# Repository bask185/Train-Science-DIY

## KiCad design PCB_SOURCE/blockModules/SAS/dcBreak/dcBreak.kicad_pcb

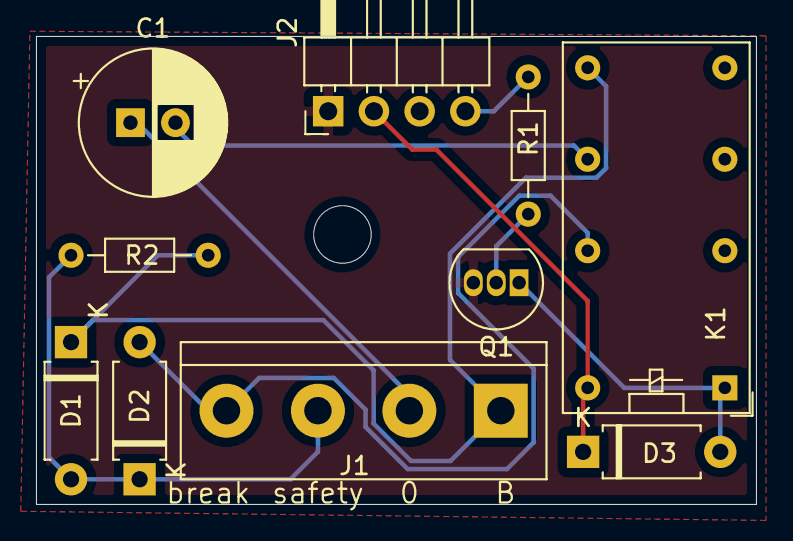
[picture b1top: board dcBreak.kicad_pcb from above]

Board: 2 copper layers, 40.0 x 26.0 mm, 11 parts (0 on the bottom side), 10 nets.

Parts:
C1: CP; CP_Radial_D8.0mm_P2.50mm
D1, D2, D3: D; D_A-405_P7.62mm_Horizontal
J1: Screw_Terminal_01x02; TerminalBlock_bornier-4_P5.08mm
J2: Conn_01x04_Male; PinHeader_1x04_P2.54mm_Horizontal
K1: AZ850-x; Relay_DPDT_Omron_G5V-2
Q1: BC547; TO-92_Inline
R1, R2: R; R_Axial_DIN0204_L3.6mm_D1.6mm_P7.62mm_Horizontal
d: MountingHole_3.2mm_M3

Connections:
+5V: D3.1, J2.2, K1.10
/B: D1.1, J1.1, K1.9, R2.1
/O: C1.1, J1.2
/break: D2.2, J1.4, K1.8
/safety: D1.2, D2.1, J1.3, R2.2
GND: J2.1, Q1.3
unnamed: C1.2, K1.7
unnamed: D3.2, K1.1, Q1.1
unnamed: J2.4, R1.2
unnamed: Q1.2, R1.1

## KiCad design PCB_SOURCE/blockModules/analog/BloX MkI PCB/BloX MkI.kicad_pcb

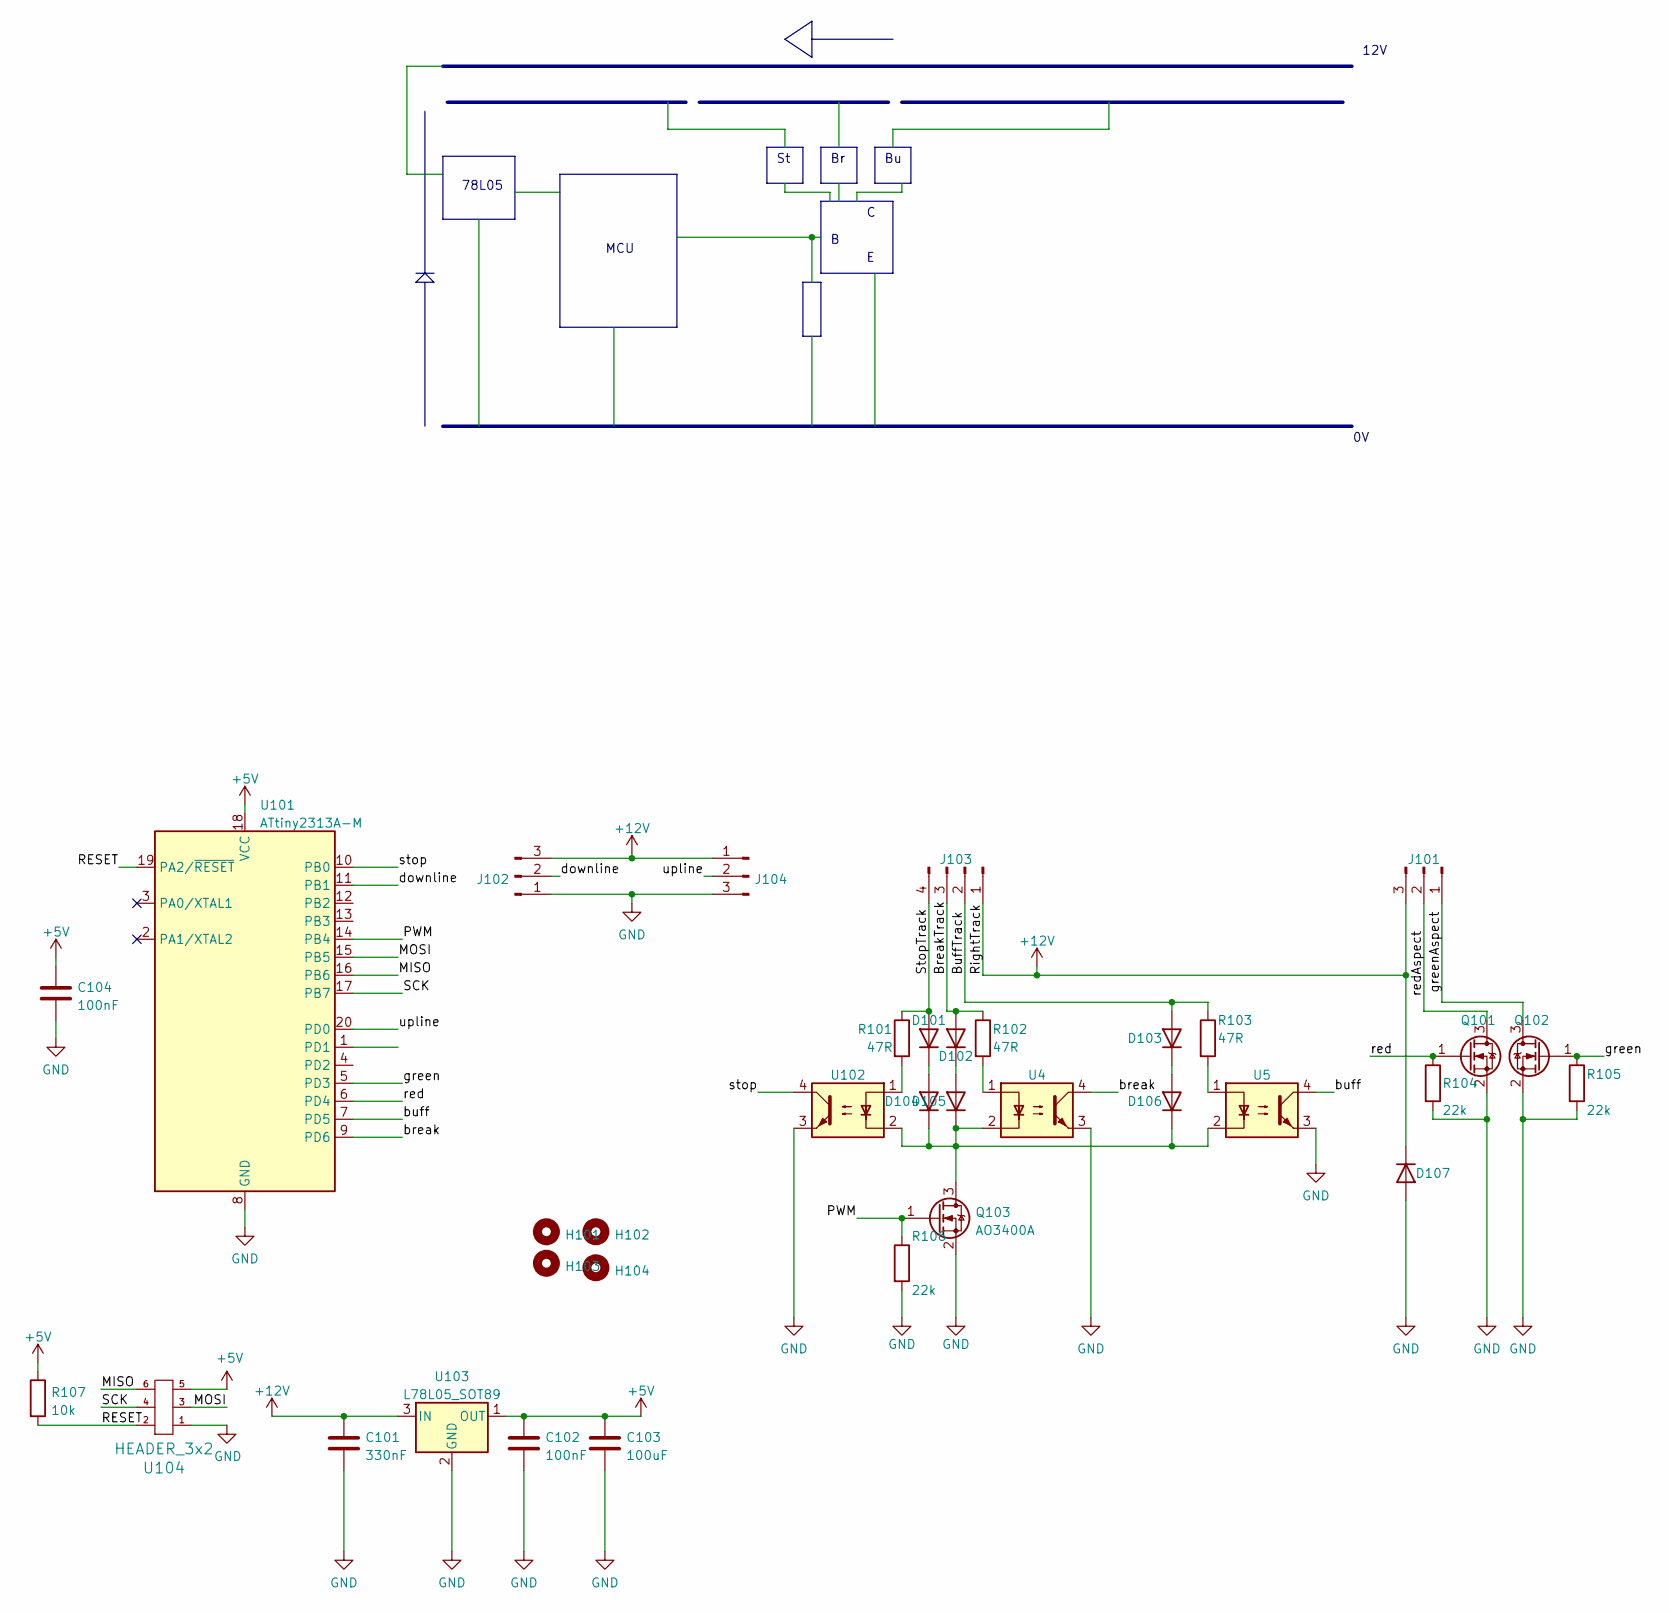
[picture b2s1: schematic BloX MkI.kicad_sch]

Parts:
C101: 330nF; C_0603_1608Metric_Pad1.08x0.95mm_HandSolder; JLCPCB Part# C1615
C102, C104: 100nF; C_0603_1608Metric_Pad1.08x0.95mm_HandSolder; JLCPCB Part# C14663
C103: 100uF; C_1206_3216Metric_Pad1.33x1.80mm_HandSolder; JLCPCB Part# C15008
D101, D102, D103, D104, D105, D106, D107: SM4007; D_SOD-123F; JLCPCB Part# C64898
H101, H102, H103, H104: MountingHole; MountingHole_3.2mm_M3
J101, J102, J104: Conn_01x03_Male; PhoenixContact_MC_1,5_3-G-3.81_1x03_P3.81mm_Horizontal
J103: Conn_01x04_Male; PhoenixContact_MC_1,5_4-G-3.81_1x04_P3.81mm_Horizontal
Q101, Q102, Q103: AO3400A; SOT-23; JLCPCB Part# C20917
R101, R102, R103: 47R; R_0805_2012Metric_Pad1.20x1.40mm_HandSolder; JLCPCB Part# C17714
R104, R105, R106: 22k; R_0805_2012Metric_Pad1.20x1.40mm_HandSolder; JLCPCB Part# C17560
R107: 10k; R_0603_1608Metric_Pad0.98x0.95mm_HandSolder; JLCPCB Part# C25804
U4, U5, U102: SFH617A-3X017T; SMDIP-4_W9.53mm_Clearance8mm
U101: ATtiny2313A-M; MLF-20-1EP_4x4mm_P0.5mm_EP2.6x2.6mm; JLCPCB Part# C185530
U103: L78L05_SOT89; SOT-89-3; JLCPCB Part# C71136
U104: HEADER_3x2; PinSocket_2x03_P1.27mm_Vertical

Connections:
+5V: C102.1, C103.1, C104.1, R107.1, U101.18 (VCC), U103.1 (OUT), U104.5
+12V: C101.1, D107.1 (K), J101.3, J102.3, J103.1, J104.1, U103.3 (IN)
/BreakTrack: D102.2 (A), J103.3, R102.1
/BuffTrack: D103.2 (A), J103.2, R103.1
/MISO: U101.16 (PB6), U104.6
/MOSI: U101.15 (PB5), U104.3
/PWM: Q103.1 (G), R106.1, U101.14 (PB4)
/RESET: R107.2, U101.19 (PA2/~RESET), U104.2
/SCK: U101.17 (PB7), U104.4
/StopTrack: D101.2 (A), J103.4, R101.1
/break: U4.4, U101.9 (PD6)
/buff: U5.4, U101.7 (PD5)
/downline: J102.2, U101.11 (PB1)
/green: Q102.1 (G), R105.1, U101.5 (PD3)
/greenAspect: J101.1, Q102.3 (D)
/red: Q101.1 (G), R104.1, U101.6 (PD4)
/redAspect: J101.2, Q101.3 (D)
/stop: U101.10 (PB0), U102.4
/upline: J104.2, U101.20 (PD0)
GND: C101.2, C102.2, C103.2, C104.2, D107.2 (A), J102.1, J104.3, Q101.2 (S), Q102.2 (S), Q103.2 (S), R104.2, R105.2, R106.2, U4.3, U5.3, U101.8 (GND), U101.21 (GND), U102.3, U103.2 (GND), U104.1
unnamed: D101.1 (K), D104.2 (A)
unnamed: D102.1 (K), D105.2 (A)
unnamed: D103.1 (K), D106.2 (A)
unnamed: D104.1 (K), D105.1 (K), D106.1 (K), Q103.3 (D), U4.2, U5.2, U102.2
unnamed: R101.2, U102.1
unnamed: R102.2, U4.1
unnamed: R103.2, U5.1

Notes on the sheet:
78L05
MCU
12V

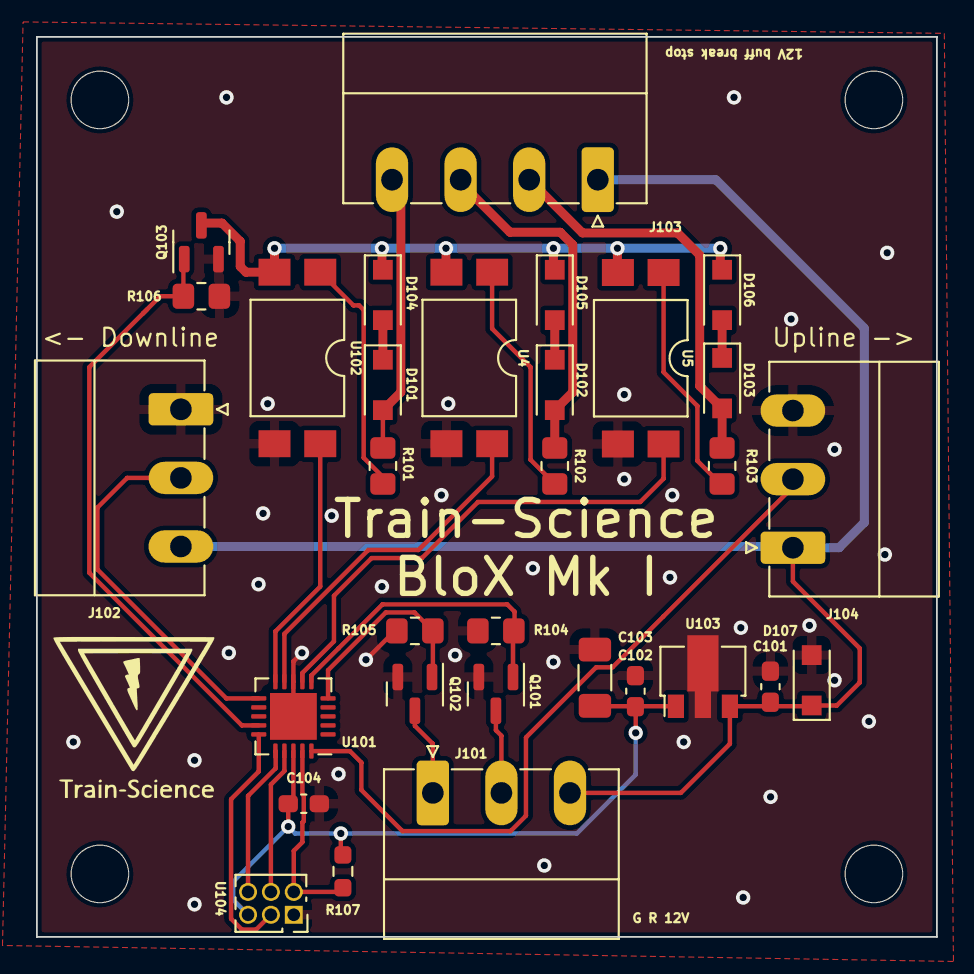
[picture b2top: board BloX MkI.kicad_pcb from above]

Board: 2 copper layers, 50.0 x 50.0 mm, 35 parts (0 on the bottom side), 27 nets.

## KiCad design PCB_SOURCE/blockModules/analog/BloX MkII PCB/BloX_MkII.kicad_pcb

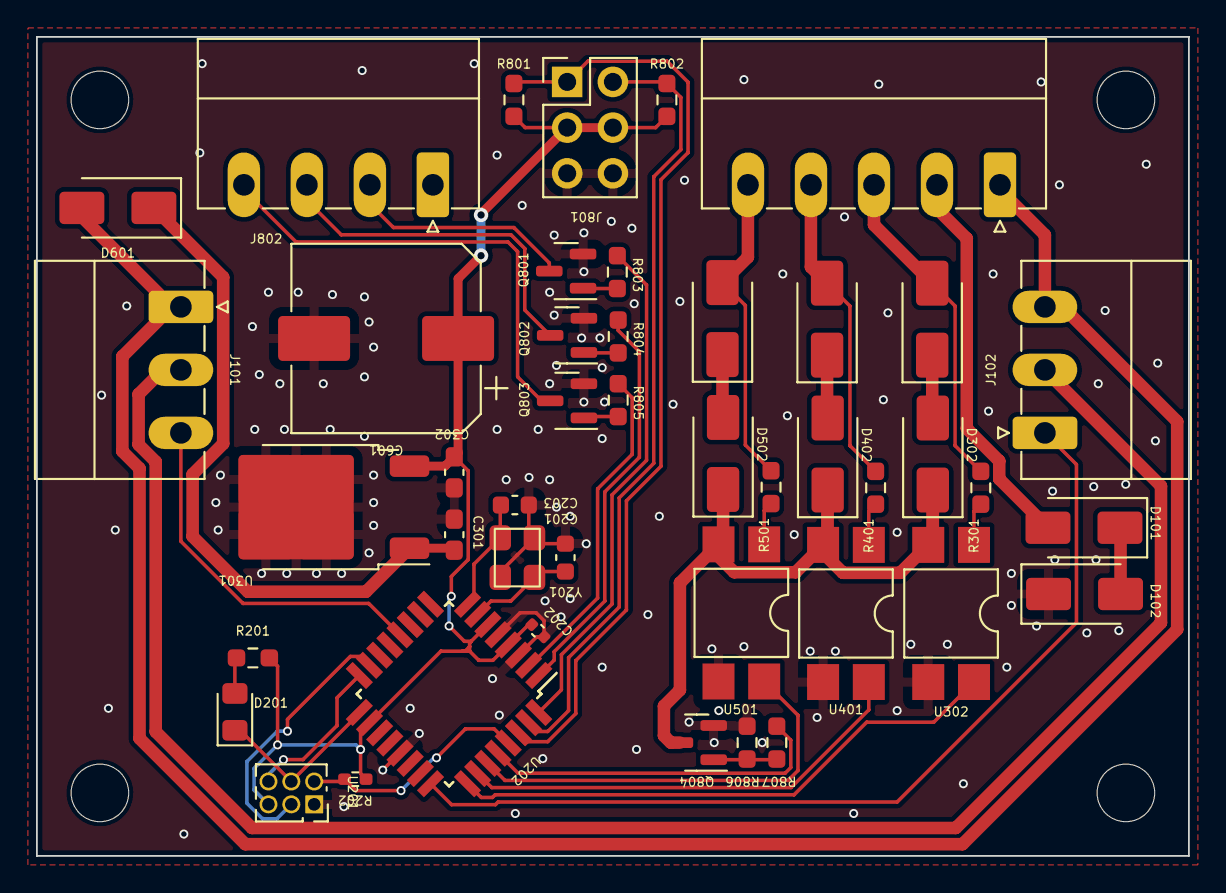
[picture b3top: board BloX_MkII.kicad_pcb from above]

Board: 2 copper layers, 64.0 x 45.5 mm, 44 parts (0 on the bottom side), 42 nets.

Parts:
C201, C203: 12pF; C_0603_1608Metric
C202: 100nF; C_0402_1005Metric
C301: 330nF; C_0603_1608Metric_Pad1.08x0.95mm_HandSolder
C302: 100nF; C_0603_1608Metric_Pad1.08x0.95mm_HandSolder
C601: 220uF; CP_Elec_10x10
D101, D102, D301, D302, D401, D402, D501, D502, D601: SS53; D_SMA
D201: LED; LED_0805_2012Metric_Pad1.15x1.40mm_HandSolder
J101, J102: Screw_Terminal_01x04; PhoenixContact_MC_1,5_3-G-3.5_1x03_P3.50mm_Horizontal
J103: Screw_Terminal_01x04; PhoenixContact_MC_1,5_5-G-3.5_1x05_P3.50mm_Horizontal
J801: Conn_02x03_Odd_Even; PinHeader_2x03_P2.54mm_Vertical
J802: Conn_01x04; PhoenixContact_MC_1,5_4-G-3.5_1x04_P3.50mm_Horizontal
Q801, Q802, Q803: NPN_TOR; SOT-23
Q804: AO3400A; SOT-23
R201: 6k2; R_0603_1608Metric_Pad0.98x0.95mm_HandSolder
R202: 10k; R_0402_1005Metric_Pad0.72x0.64mm_HandSolder
R301, R401, R501: 47R; R_0603_smalltext
R801, R802: 10k; R_0603_smalltext
R803, R804, R805: 1k; R_0603_smalltext
R806: 22k; R_0603_smalltext
R807: 22R; R_0603_smalltext
U201: HEADER_3x2; PinSocket_2x03_P1.27mm_Vertical
U202: ATmega328-A; TQFP-32_7x7mm_P0.8mm
U301: LM78M05_TO252; TO-252-2
U302, U401, U501: EL817S; SMDIP-4_W7.62mm
Y201: Crystal_GND2; crystal_arduino

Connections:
+5V: C202.1, C302.1, C601.1, J801.3, J801.4, R201.1, R202.1, R801.2, R802.2, U201.5, U202.4 (VCC), U202.6 (VCC), U202.18 (AVCC), U301.3 (VO)
+12V: C301.1, D601.1 (K), U301.1 (VI)
/Brake/COM: D302.1 (K), D402.1 (K), D502.1 (K), Q804.3 (D), U302.2, U401.2, U501.2
/Brake/TRACK: D401.2 (A), J103.4, R401.1
/Buffer/TRACK: D301.2 (A), J103.3, R301.1
/CPU/MISO: U201.6, U202.16 (PB4)
/CPU/MOSI: U201.3, U202.15 (PB3)
/CPU/PWM: R807.2, U202.28 (PC5)
/CPU/SCK: D201.1 (K), U201.4, U202.17 (PB5)
/CPU/X1: C201.2, U202.7 (XTAL1/PB6), Y201.1
/CPU/X2: C203.2, U202.8 (XTAL2/PB7), Y201.3
/CPU/dist: J801.1, R801.1, U202.30 (PD0)
/CPU/downline: J101.3, U202.12 (PB0)
/CPU/green: R803.1, U202.32 (PD2)
/CPU/main: J801.2, R802.1, U202.31 (PD1)
/CPU/red: R805.1, U202.2 (PD4)
/CPU/reset: R202.2, U201.2, U202.29 (~RESET/PC6)
/CPU/upline: J102.1, U202.24 (PC1)
/CPU/yellow: R804.1, U202.1 (PD3)
/Stop/TRACK: D501.2 (A), J103.5, R501.1
/brake: U202.26 (PC3), U401.4
/buffer: U202.25 (PC2), U302.4
/ring_left: J101.2, J102.2
/ring_right: D601.2 (A), J101.1, J102.3, J103.1
/signals/green_amp: J802.2, Q801.3 (C)
/signals/red_amp: J802.4, Q803.3 (C)
/signals/yellow_amp: J802.3, Q802.3 (C)
/stop: U202.27 (PC4), U501.4
/track_left: D101.2 (A), J103.2
GND: C201.1, C202.2, C203.1, C301.2, C302.2, C601.2, D102.1 (K), J801.5, J801.6, Q801.2 (E), Q802.2 (E), Q803.2 (E), Q804.2 (S), R806.2, U201.1, U202.3 (GND), U202.5 (GND), U202.21 (GND), U301.2 (GND), U302.3, U401.3, U501.3, Y201.2 (GND), Y201.4 (GND)
unnamed: D101.1 (K), D102.2 (A)
unnamed: D201.2 (A), R201.2
unnamed: D301.1 (K), D302.2 (A)
unnamed: D401.1 (K), D402.2 (A)
unnamed: D501.1 (K), D502.2 (A)
unnamed: Q801.1 (B), R803.2
unnamed: Q802.1 (B), R804.2
unnamed: Q803.1 (B), R805.2
unnamed: Q804.1 (G), R806.1, R807.1
unnamed: R301.2, U302.1
unnamed: R401.2, U401.1
unnamed: R501.2, U501.1

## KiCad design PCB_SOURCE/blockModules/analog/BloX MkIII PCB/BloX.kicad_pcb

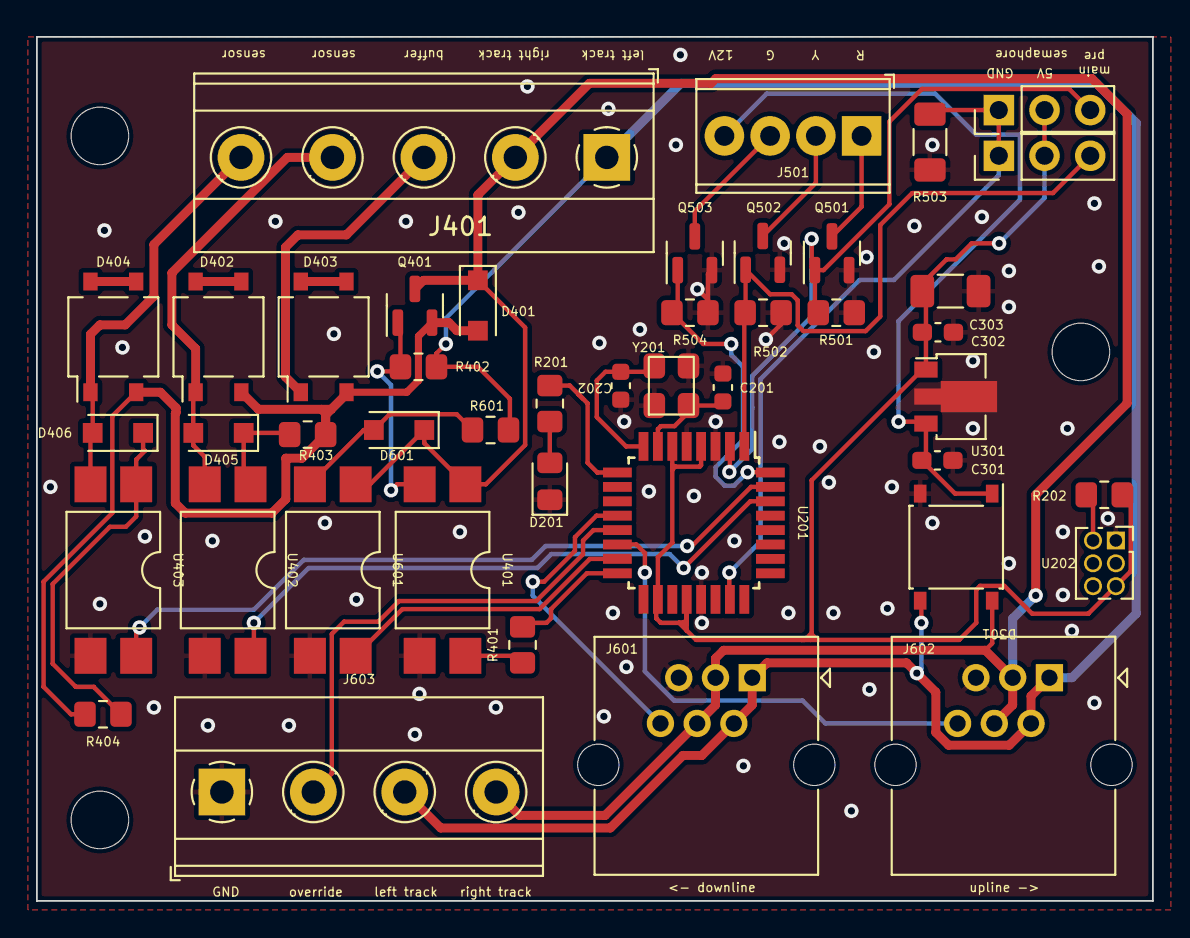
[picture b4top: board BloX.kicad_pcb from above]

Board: 2 copper layers, 62.0 x 48.0 mm, 44 parts (0 on the bottom side), 36 nets.

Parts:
C201, C202: 12pF; C_0603_1608Metric
C301: 330nF; C_0603_1608Metric_Pad1.08x0.95mm_HandSolder
C302: 100nF; C_0603_1608Metric_Pad1.08x0.95mm_HandSolder
C303: 100uF; C_1206_3216Metric_Pad1.33x1.80mm_HandSolder
D201: yellow_LED; LED_0805_2012Metric_Pad1.15x1.40mm_HandSolder
D301: D_Bridge_+-AA; Diode_Bridge_Diotec_ABS
D401, D405, D406, D601: SM4007; D_SOD-123F
D402, D403, D404: MB6S; TO-269AA
J401: tracks; TerminalBlock_Phoenix_MKDS-1,5-5-5.08_1x05_P5.08mm_Horizont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
J501: signals; TerminalBlock_Phoenix_MPT-0,5-4-2.54_1x04_P2.54mm_Horizontal
J601, J602: RJ12; RJ25_Wayconn_MJEA-660X1_Horizontal
J603: Screw_Terminal_01x04; TerminalBlock_Phoenix_MKDS-1,5-4-5.08_1x04_P5.08mm_Horizont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
Q401, Q501, Q502, Q503: AO3400A; SOT-23
R201, R202: R; R_0805_2012Metric_Pad1.20x1.40mm_HandSolder
R401: 330R; R_0805_2012Metric_Pad1.20x1.40mm_HandSolder
R402, R501, R502, R504: 100k; R_0805_2012Metric_Pad1.20x1.40mm_HandSolder
R403, R404: 33R; R_0805_2012Metric_Pad1.20x1.40mm_HandSolder
R503: 0R1; R_1206_3216Metric_Pad1.30x1.75mm_HandSolder
R601: 680R; R_0805_2012Metric_Pad1.20x1.40mm_HandSolder
U201: ATmega328-A; TQFP-32_7x7mm_P0.8mm
U202: HEADER_3x2; PinSocket_2x03_P1.27mm_Vertical
U301: L78L05_SOT89; SOT-89-3
U401, U402, U403, U601: EL817; SMDIP-4_W9.53mm
Y201: crystal_arduino
servo501, servo502: Conn_01x03_Male; PinHeader_1x03_P2.54mm_Vertical

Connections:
+5V: C302.1, C303.1, R202.1, U201.4 (VCC), U201.6 (VCC), U201.18 (AVCC), U201.20 (AREF), U202.5, U301.1 (OUT), servo501.2, servo502.2
+12V: C301.1, D301.1 (+), J501.4, U301.3 (IN)
/controller/RESET: R202.2, U202.2
/controller/X1: C201.2, U201.7 (XTAL1/PB6), Y201.1
/controller/X2: C202.2, U201.8 (XTAL2/PB7), Y201.3
/controller/statusLed: R201.1, U201.9 (PD5)
/mosfets/buffer: D403.1, J401.3
/mosfets/track_downline: D402.1, D405.2 (A), J401.4, U402.2
/mosfets/track_upline: D404.1, D406.2 (A), J401.5, U403.2
GND: C201.1, C202.1, C301.2, C302.2, C303.2, D201.1 (K), D301.2 (-), J601.5, J602.5, J603.1, Q501.2 (S), Q502.2 (S), Q503.2 (S), R501.2, R502.2, R503.2, R504.2, U201.3 (GND), U201.5 (GND), U201.21 (GND), U202.1, U301.2 (GND), U401.3, U402.3, U403.3, U601.3, Y201.2 (GND), Y201.4 (GND)
unnamed: D201.2 (A), R201.2
unnamed: D401.2 (A), D402.2, D403.2, D404.2, Q401.2 (S), R403.1, R404.1
unnamed: D402.3 (+), D402.4 (-)
unnamed: D403.3 (+), D403.4 (-)
unnamed: D404.3 (+), D404.4 (-)
unnamed: D405.1 (K), R403.2, U402.1
unnamed: D406.1 (K), R404.2, U403.1
unnamed: D601.2 (A), R601.1, U601.2
unnamed: J501.1, Q501.3 (D)
unnamed: J501.2, Q502.3 (D)
unnamed: J501.3, Q503.3 (D)
unnamed: Q401.1 (G), R402.1, U401.2
unnamed: R401.1, U401.4
PWM: R401.2, U201.16 (PB4)
direction: U201.15 (PB3), U601.4
downLine: J601.6, U201.12 (PB0)
greenLed: Q503.1 (G), R504.1, U201.32 (PD2)
leftTrack: D301.3, J401.1, J601.1, J601.2, J602.1, J602.2, J603.3, R402.2, R601.2
override: J603.2, U201.13 (PB1)
rightTrack: D301.4, D401.1 (K), D601.1 (K), J401.2, J601.3, J601.4, J602.3, J602.4, J603.4, Q401.3 (D), U401.1, U601.1
semaphore_main: Q502.1 (G), R502.1, U201.1 (PD3), servo502.3
semaphore_pre: Q501.1 (G), R501.1, U201.2 (PD4), servo501.3
sensor_downline: U201.30 (PD0), U402.4
sensor_upline: U201.31 (PD1), U403.4
servoDetect: R503.1, U201.23 (PC0), servo501.1, servo502.1
upLine: J602.6, U201.14 (PB2)

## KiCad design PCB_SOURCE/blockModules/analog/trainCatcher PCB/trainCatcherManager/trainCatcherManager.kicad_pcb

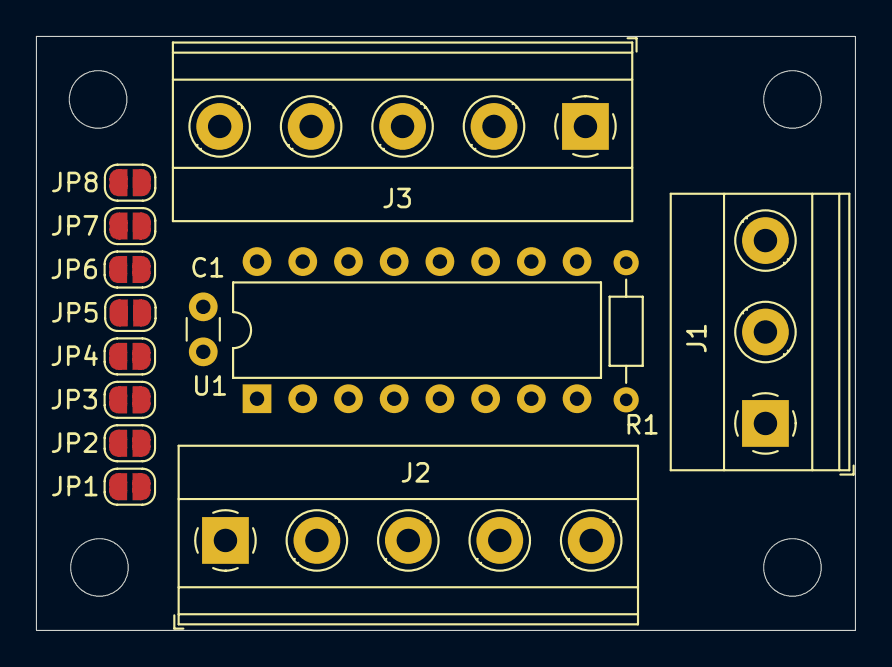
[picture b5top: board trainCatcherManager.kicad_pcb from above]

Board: 2 copper layers, 45.5 x 33.0 mm, 14 parts (0 on the bottom side), 14 nets, no tracks yet.

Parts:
C1: C; C_Disc_D3.0mm_W1.6mm_P2.50mm
J1: screw; TerminalBlock_Phoenix_MKDS-1,5-3-5.08_1x03_P5.08mm_Horizont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
J2, J3: Screw_Terminal_01x10; TerminalBlock_Phoenix_MKDS-1,5-5-5.08_1x05_P5.08mm_Horizont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
JP1, JP2, JP3, JP4, JP5, JP6, JP7, JP8: ju; SolderJumper-2_P1.3mm_Open_RoundedPad1.0x1.5mm
R1: 100k; R_Axial_DIN0204_L3.6mm_D1.6mm_P7.62mm_Horizontal
U1: 4017; DIP-16_W7.62mm

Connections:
+5V: C1.1, J1.2, U1.16
/out1: J2.1, U1.3
/out2: J2.2, U1.2
/out3: J2.3, JP1.2, U1.4
/out4: J2.4, JP2.2, U1.7
/out5: J2.5, JP3.2, U1.10
/out6: J3.1, JP4.2, U1.1
/out7: J3.2, JP5.2, U1.5
/out8: J3.3, JP6.2, U1.6
/out9: J3.4, JP7.2, U1.9
/out10: J3.5, JP8.2, U1.11
/rec: J1.3, U1.14
GND: C1.2, J1.1, R1.2, U1.8, U1.13
unnamed: JP1.1, JP2.1, JP3.1, JP4.1, JP5.1, JP6.1, JP7.1, JP8.1, R1.1, U1.15

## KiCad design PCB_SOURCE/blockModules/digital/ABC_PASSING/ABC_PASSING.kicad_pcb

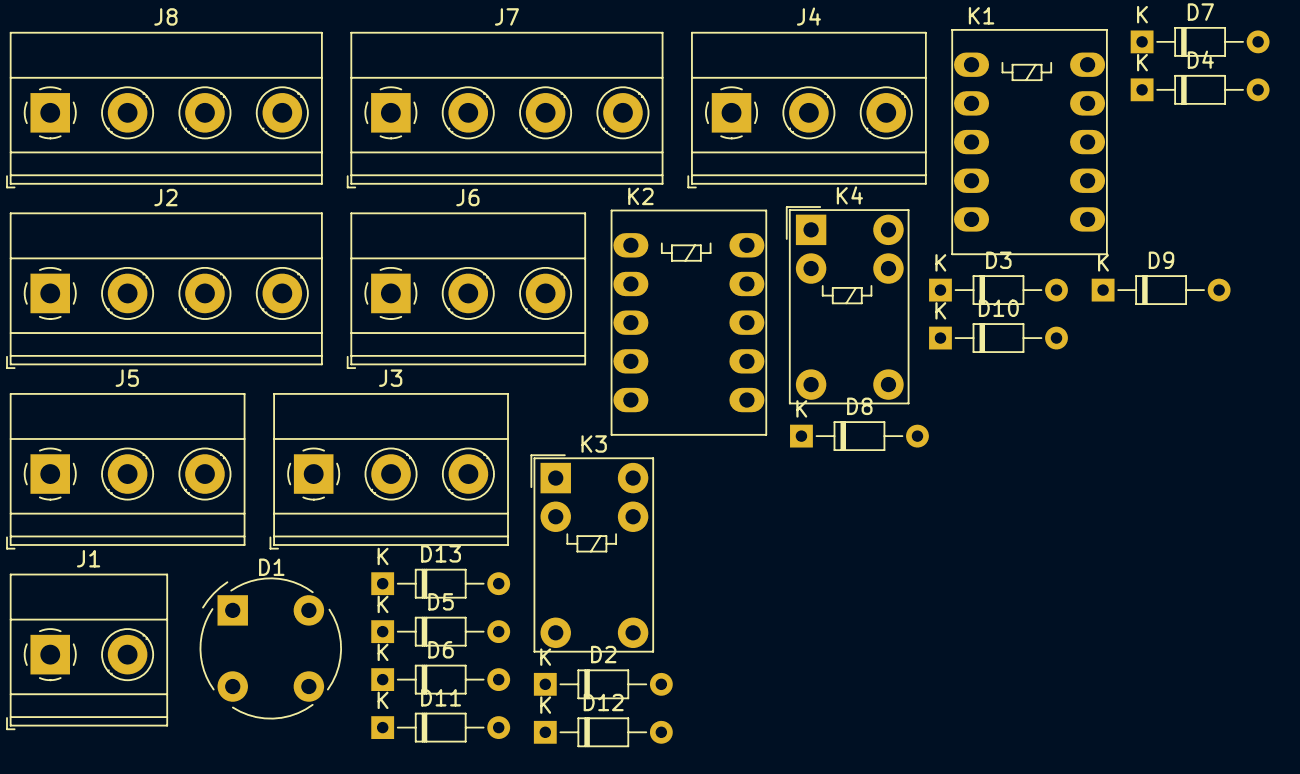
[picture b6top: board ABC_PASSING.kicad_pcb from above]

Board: 2 copper layers, 25 parts (0 on the bottom side), 26 nets, no tracks yet.

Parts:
D1: D_Bridge_+A-A; Diode_Bridge_Round_D9.0mm
D2, D3, D4, D5, D6, D7, D8, D9, D10, D11, D12, D13: D; D_DO-34_SOD68_P7.62mm_Horizontal
J1: Screw_Terminal_01x02; TerminalBlock_Phoenix_MKDS-1,5-2-5.08_1x02_P5.08mm_Horizont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
J2: Rails; TerminalBlock_Phoenix_MKDS-1,5-4-5.08_1x04_P5.08mm_Horizont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
J3, J4: signal; TerminalBlock_Phoenix_MKDS-1,5-3-5.08_1x03_P5.08mm_Horizont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
J5: Points; TerminalBlock_Phoenix_MKDS-1,5-3-5.08_1x03_P5.08mm_Horizont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
J6: points; TerminalBlock_Phoenix_MKDS-1,5-3-5.08_1x03_P5.08mm_Horizont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
J7, J8: reed; TerminalBlock_Phoenix_MKDS-1,5-4-5.08_1x04_P5.08mm_Horizont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
K1, K2: AZ850P2-x; Relay_DPDT_FRT5
K3, K4: G5V-1; Relay_SPDT_Omron_G5V-1

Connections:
/DCC_A: D8.2 (A), D13.1 (K), J2.2, K2.3
/DCC_B: D6.1 (K), D7.2 (A), J2.3, K1.3
/go1: J7.4, K2.5, K3.2
/go2: J8.2, K1.5, K4.2
/pow1: D1.4, J1.1
/pow2: D1.2, J1.2
/stop1: J7.2, K1.6
/stop2: J8.4, K2.6
/track1: D2.2 (A), D7.1 (K), J2.1, K1.2
/track2: D8.1 (K), D9.2 (A), J2.4, K2.2
GND: D1.3 (-), J7.1, J7.3, J8.1, J8.3, K1.8, K2.8, K3.5, K3.6, K4.5, K4.6
unnamed: D2.1 (K), D3.2 (A)
unnamed: D3.1 (K), D4.2 (A)
unnamed: D4.1 (K), D5.2 (A)
unnamed: D5.1 (K), D6.2 (A)
unnamed: D10.1 (K), D11.2 (A)
unnamed: D9.1 (K), D10.2 (A)
unnamed: D11.1 (K), D12.2 (A)
unnamed: D12.1 (K), D13.2 (A)
unnamed: J3.1, K1.7
unnamed: J3.3, K1.9
unnamed: J4.1, K2.9
unnamed: J4.3, K2.7
unnamed: J5.1, J6.3, K4.10
unnamed: J5.3, J6.1, K3.10
VCC: D1.1 (+), J3.2, J4.2, J5.2, J6.2, K1.1, K1.10, K2.1, K2.10, K3.9, K4.9

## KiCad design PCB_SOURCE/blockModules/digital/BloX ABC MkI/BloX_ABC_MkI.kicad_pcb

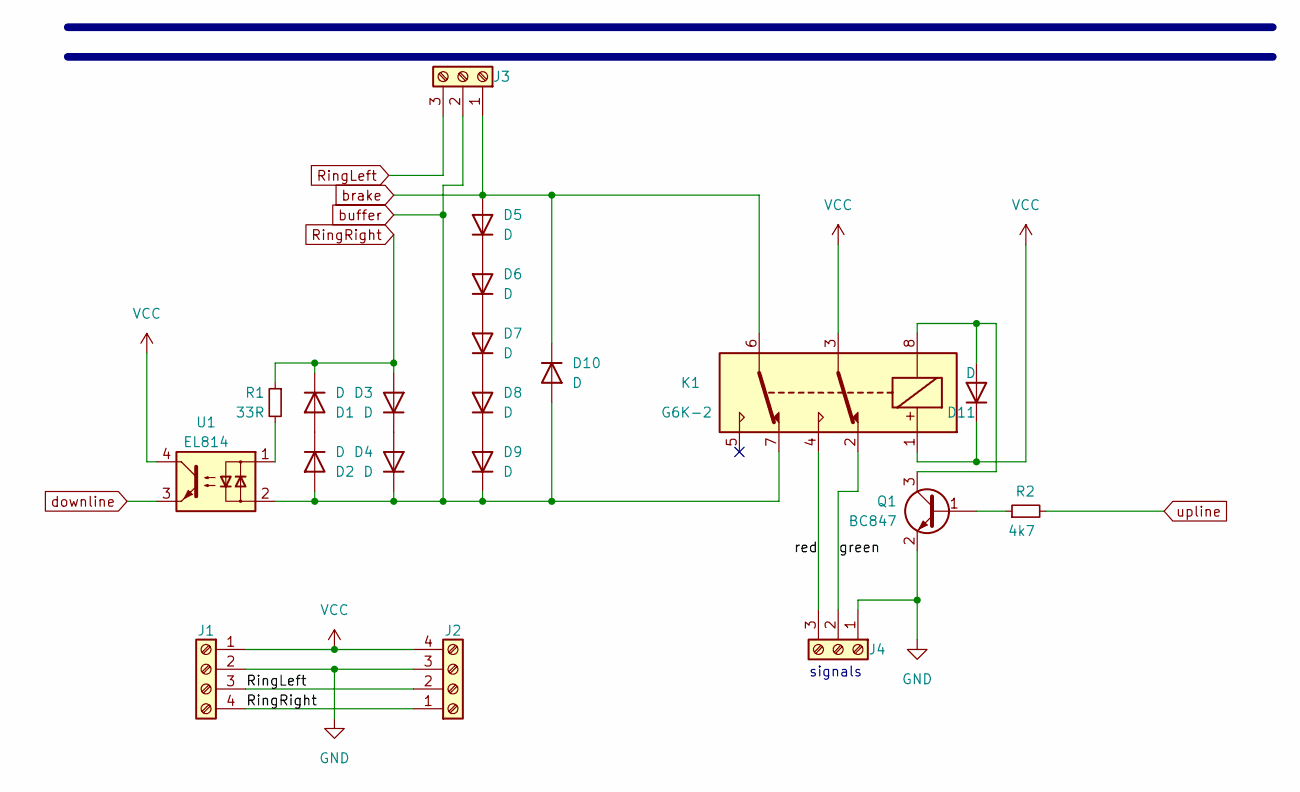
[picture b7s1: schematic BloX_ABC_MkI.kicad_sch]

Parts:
D1, D2, D3, D4, D5, D6, D7, D8, D9, D10, D11: D; D_SOD-123F
J1, J2: Screw_Terminal_01x04; TerminalBlock_Phoenix_MKDS-1,5-4-5.08_1x04_P5.08mm_Horizont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
J3, J4: Screw_Terminal_01x03; TerminalBlock_Phoenix_MKDS-1,5-3-5.08_1x03_P5.08mm_Horizont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
K1: G6K-2; Relay_DPDT_Omron_G6K-2F-Y
Q1: BC847; SOT-23
R1: 33R; R_0805_2012Metric_Pad1.20x1.40mm_HandSolder
R2: 4k7; R_0805_2012Metric_Pad1.20x1.40mm_HandSolder
U1: EL814; SMDIP-4_W9.53mm

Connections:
/green: J4.2, K1.2
/red: J4.3, K1.4
GND: J1.2, J2.3, J4.1, Q1.2 (E)
unnamed: D1.2 (A), D2.1 (K)
unnamed: D3.1 (K), D4.2 (A)
unnamed: D5.1 (K), D6.2 (A)
unnamed: D6.1 (K), D7.2 (A)
unnamed: D7.1 (K), D8.2 (A)
unnamed: D8.1 (K), D9.2 (A)
unnamed: D11.2 (A), K1.8, Q1.3 (C)
unnamed: Q1.1 (B), R2.1
unnamed: R1.2, U1.1
RingLeft: J1.3, J2.2, J3.3
RingRight: D1.1 (K), D3.2 (A), J1.4, J2.1, R1.1
VCC: D11.1 (K), J1.1, J2.4, K1.1, K1.3, U1.4
brake: D5.2 (A), D10.1 (K), J3.1, K1.6
buffer: D2.2 (A), D4.1 (K), D9.1 (K), D10.2 (A), J3.2, K1.7, U1.2
downline: U1.3
upline: R2.2

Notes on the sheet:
signals

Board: 2 copper layers, 20 parts (0 on the bottom side), 17 nets, no tracks yet.

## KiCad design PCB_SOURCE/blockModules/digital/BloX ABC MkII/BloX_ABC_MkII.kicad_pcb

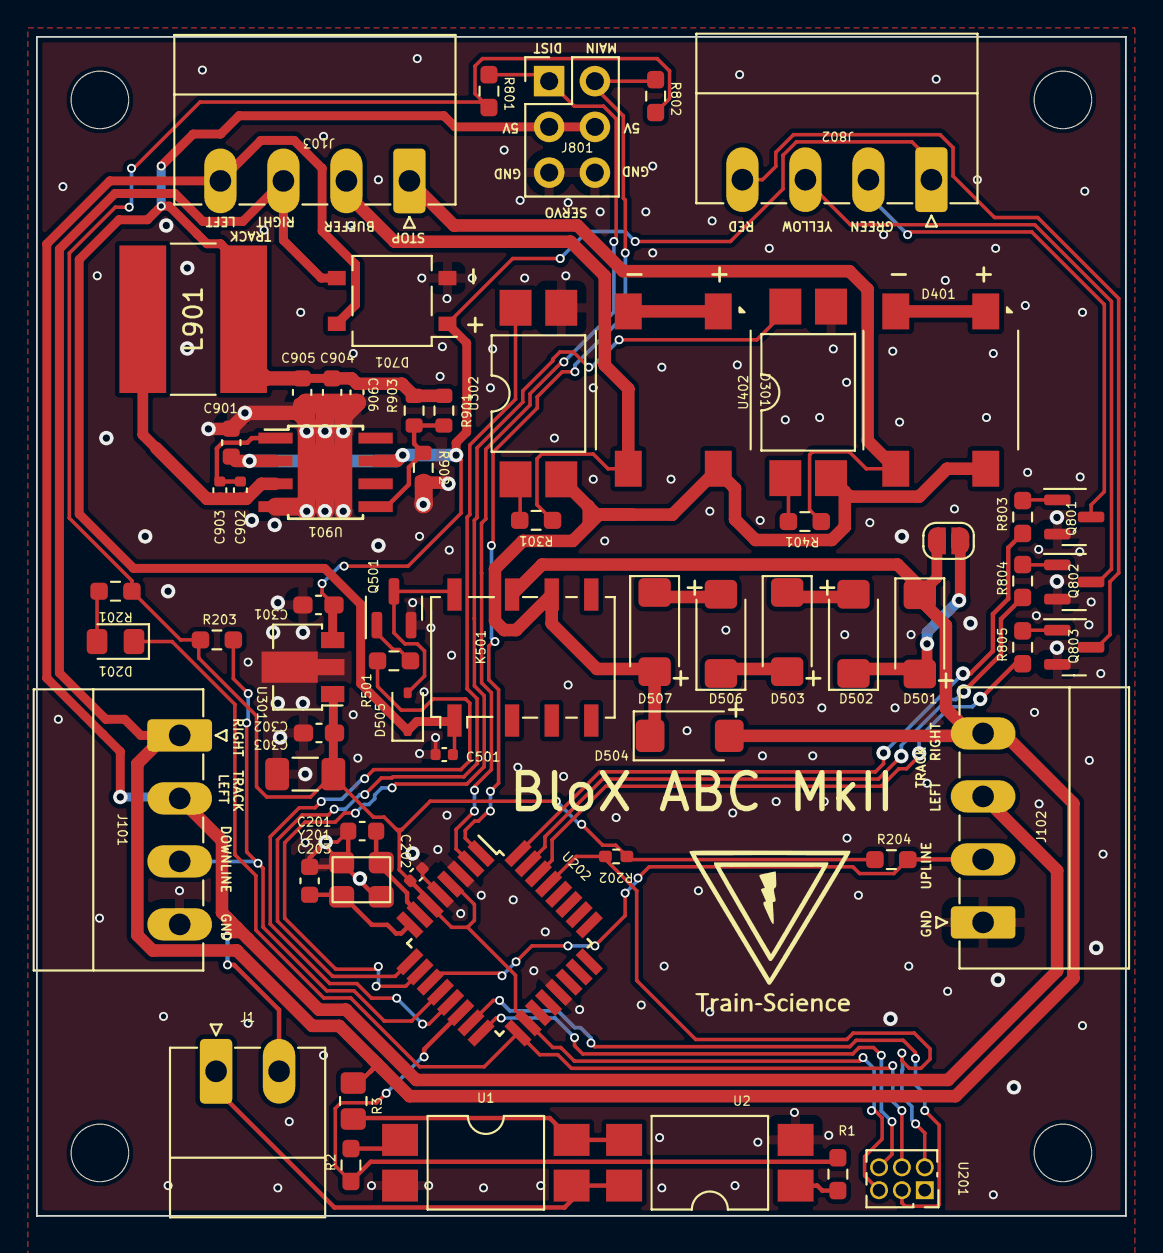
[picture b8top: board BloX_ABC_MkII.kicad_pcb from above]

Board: 2 copper layers, 60.5 x 65.5 mm, 64 parts (0 on the bottom side), 50 nets.

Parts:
C201, C203: 12pF; C_0603_1608Metric
C202, C501, C902, C906: 100nF; C_0402_1005Metric
C301: 330nF; C_0603_1608Metric_Pad1.08x0.95mm_HandSolder
C302: 100nF; C_0603_1608Metric_Pad1.08x0.95mm_HandSolder
C303: 100uF; C_1206_3216Metric_Pad1.33x1.80mm_HandSolder
C901, C904, C905: 22uF; C_0603_1608Metric
C903: 22nF; C_0402_1005Metric
D201: LED; LED_0805_2012Metric_Pad1.15x1.40mm_HandSolder
D301, D401: D_Bridge_+-AA; DB201S
D501, D502, D503, D504, D506, D507: S2MF; S2MF_DIODE
D505: 1N4148WS; D_SOD-323
D701: MB10S; TO-269AA
J1: Screw_Terminal_01x02; PhoenixContact_MC_1,5_2-G-3.5_1x02_P3.50mm_Horizontal
J101, J102, J103: Screw_Terminal_01x04; PhoenixContact_MC_1,5_4-G-3.5_1x04_P3.50mm_Horizontal
J801: Conn_02x03_Odd_Even; PinHeader_2x03_P2.54mm_Vertical
J802: Conn_01x04; PhoenixContact_MC_1,5_4-G-3.5_1x04_P3.50mm_Horizontal
JP501: SolderJumper_2_Open; SolderJumper-2_P1.3mm_Open_RoundedPad1.0x1.5mm
K501: G6K-2F-Y-TR DC5; Relay_DPDT_Omron_G6K-2F-Y
L901: L; L_Bourns-SRN8040_8x8.15mm
Q501, Q801, Q802, Q803: NPN_TOR; SOT-23
R1, R2: 330R; R_0603_smalltext
R3: 3k3; R_0805_handsolder-smalltext
R201: 6k2; R_0603_1608Metric_Pad0.98x0.95mm_HandSolder
R202: 10k; R_0402_1005Metric_Pad0.72x0.64mm_HandSolder
R203, R204, R801, R802: 10k; R_0603_smalltext
R301, R401: 47R; R_0603_smalltext
R501, R803, R804, R805: 1k; R_0603_smalltext
R901: 220k; R_0603_1608Metric
R902: 20k; R_0603_1608Metric
R903: 150k; R_0603_1608Metric
U1, U2: EL817S; SMDIP-4_W9.53mm
U201: HEADER_3x2; PinSocket_2x03_P1.27mm_Vertical
U202: ATmega328-A; TQFP-32_7x7mm_P0.8mm
U301: L78L05_SOT89; SOT-89-3
U302, U402: EL814; SMDIP-4_W9.53mm
U901: MT2499A; TI_SO-PowerPAD-8
Y201: Crystal_GND2; crystal_arduino

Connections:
+5V: C202.1, C302.1, C303.1, R201.1, R202.1, R203.1, R204.1, R801.2, R802.2, U201.5, U202.4 (VCC), U202.6 (VCC), U202.18 (AVCC), U301.1 (OUT)
+5VA: C501.1, C904.1, C905.1, C906.1, D505.1 (K), J801.3, J801.4, K501.1, L901.2, R901.1, R903.2
/ABC/COM: D301.4, D401.4, D504.1 (K), D507.2 (A), K501.6, U302.2, U402.2
/ABC/TTL: R501.2, U202.13 (PB1)
/CPU/MISO: U201.6, U202.16 (PB4)
/CPU/MOSI: U201.3, U202.15 (PB3)
/CPU/S1: U202.9 (PD5), U302.4
/CPU/S2: U202.10 (PD6), U402.4
/CPU/SCK: D201.1 (K), U201.4, U202.17 (PB5)
/CPU/X1: C201.2, U202.7 (XTAL1/PB6), Y201.1
/CPU/X2: C203.2, U202.8 (XTAL2/PB7), Y201.3
/CPU/dist: J801.1, R801.1, U202.2 (PD4)
/CPU/green: R803.1, U202.32 (PD2)
/CPU/main: J801.2, R802.1, U202.1 (PD3)
/CPU/occupied: R1.1, R2.1, U202.14 (PB2)
/CPU/red: R805.1, U202.30 (PD0)
/CPU/reset: R202.2, U201.2, U202.29 (~RESET/PC6)
/CPU/yellow: R804.1, U202.31 (PD1)
/brake: D401.3, J103.1, R401.1
/buffer: D301.3, J103.2, R301.1
/downline: J101.3, R203.2, U202.12 (PB0)
/occupancy/toInput: J1.1, U1.3, U2.4
/ring_left: D701.4, J1.2, J101.2, J102.3, J103.4
/ring_right: D501.1 (K), D504.2 (A), D701.3, J101.1, J102.4, J103.3, JP501.1 (A), K501.7, R3.1
/signals/green_amp: J802.2, Q801.3 (C)
/signals/red_amp: J802.4, Q803.3 (C)
/signals/yellow_amp: J802.3, Q802.3 (C)
/up+: J102.2, R204.2, U202.11 (PD7)
GND: C201.1, C202.2, C203.1, C301.2, C302.2, C303.2, C501.2, C901.2, C904.2, C905.2, C906.2, D701.2 (-), J101.4, J102.1, J801.5, J801.6, Q501.2 (E), Q801.2 (E), Q802.2 (E), Q803.2 (E), R902.2, U1.2, U2.2, U201.1, U202.3 (GND), U202.5 (GND), U202.21 (GND), U301.2 (GND), U302.3, U402.3, U901.4 (GND), U901.9 (GND), Y201.2 (GND), Y201.4 (GND)
unnamed: D201.2 (A), R201.2
unnamed: D301.1 (+), D301.2 (-)
unnamed: D401.1 (+), D401.2 (-)
unnamed: D501.2 (A), D502.1 (K), JP501.2 (B)
unnamed: D502.2 (A), D503.1 (K)
unnamed: D503.2 (A), D506.1 (K)
unnamed: D505.2 (A), K501.8, Q501.3 (C)
unnamed: D506.2 (A), D507.1 (K)
unnamed: Q501.1 (B), R501.1
unnamed: Q801.1 (B), R803.2
unnamed: Q802.1 (B), R804.2
unnamed: Q803.1 (B), R805.2
unnamed: R1.2, U2.1
unnamed: R2.2, U1.1
unnamed: R3.2, U1.4, U2.3
unnamed: R301.2, U302.1
unnamed: R401.2, U402.1
unnamed: C902.1, C903.1, U901.1 (BS)
unnamed: R901.2, R902.1, R903.1, U901.5 (FB)
unnamed: C902.2, C903.2, L901.1, U901.3 (SW)
VCC: C301.1, C901.1, D701.1 (+), J802.1, U301.3 (IN), U901.2 (Vin), U901.7 (EN)
